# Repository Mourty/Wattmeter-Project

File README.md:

# The Wattmeter Project

This project was created for a senior design course as part of my degree path. I wanted to create a wattmeter similar to the "Kill A Watt" meters typically available, but with an important change. I wanted the ability to log the energy consumption data over time. I created a functional prototype well before I even began the class, but decided to iterate on the project and improve it. This is my first project of this scale, and I am sure it isn't perfect. In fact I'm sure it can be improved upon, but it works well enough for me.  
  
### Features
* Single Phase voltage, current, active power, reactive power, apparent power, frequency, and power factor measurement.
* LCD Display for user readable measurements.
* WiFi connectivity with RESTful API
* Configurable via SD card or web interface
* Dedicated Real time clock with automatic NTP syncing (WiFi required)
* Logs data to an SD card for optional independent operation
* Integrated UPS to prevent data loss due to power outage (100ish seconds plenty to automatically save data buffer)
* Monitoring server for remote data collection, storage, and presentation using React and python.

### Hardware
The hardware is a custom designed PCB with mostly through hole components. I chose through hole because it is what I wanted to use, more on this later.
The meter uses the Atmel M90E32 Poly-phase energy monitoring IC to do the heavy lifting of accurate power measurement. The voltage input uses a stepdown transformer and voltage divider to bring the 120VAC input voltage down around a manageable 0.6vrms. The transformer is somewhat unnecessary as a series of resistors could do the same, but this also provides some transient protection and isolation. The current measurement utilizes a current transformer with a carefully sizes burden resistor to bring the voltage down to around 0.6vrms when 20 amps is flowing though the primary of the CT. 
The power supply for the whole board is an off the shelf AC to DC power supply. This provides stable "safe" power without needed to roll my own PSU. This is fed to a super capacitor, then to the LM2621 based boost converted. The super capacitor provided an energy buffer to allow for controlled shutdown of the microcontroller in the event of a power outage. This allows time to write the current buffer of power statistics to the SD card. without this feature the SD card would either need to be written to more often with small amounts of data or the buffer would be lost during a power outage. Depending on the setting this could be multiple minutes or hours of data lost. The size of the super cap was chosen due to part availability at the time; It could easily be a quarter or even an eighth as large and still serve its purpose.
None of the components have been price optimized to a good degree. For example the diodes that are apart of the super capacitor/boost converter are rated for 2 amps, but don't ever see near that amount. These are simply what I had on hand during the design and didn't see a need to order different ones. So If you make this project too, you might want to consider components carefully, you might save some money.

I figured I could improve upon the wattmeter with the wattmeterJR. This version has fewer features, but is smaller and uses SMD components. It lacks an LCD display or the whole integrated UPS part. It is mainly to measure the same power statistics, but really requires the remote server to log the data. it is much less user friendly to build and to debug, but is cheaper and smaller. You can find this version at https://github.com/Mourty/WattmeterJR

### Firmware
I wrote the firmware with assistance from Claude.ai. I'm not the sort to go around proclaiming to be a coder, so you will find issues here. I used the Arduino IDE to develop, compile, and upload the code to the ESP32. The code is semi-organized into different files and imported where needed. The meter itself can be configured using the SD card. You will need to write the settings.ini to the SD card. In the settings you will find a place to configure your WiFi credentials as well as other settings. Many of these will seem cryptic, but most of them won't need to be modified at all. Most are actually configuration registers for the ATM90E32. You can find more on what the do in the IC's datasheet.  
  
### Service
The service is a web server that uses React for the front end and python for the backend. I again used Claude.ai to write much of the code here. The service is containerized using docker, so you should be able to get it up and running fairly easily. I used a Raspberry PI 3+, but in theory any linux computer can run this server. You will need to install docker to compose the containers and to run them. Docker *should* take care of installing other things for the containers like python and such.

I don't plan to maintain this or improve further at this time. If someone wants to improve this feel free, it won't hurt my feelings if you fork this project and do cool things with it, just give me credit for what you use. I have no idea what license this project should have given it uses a few external libraries, so before you go attempting to monetize this project you might need to check on that.

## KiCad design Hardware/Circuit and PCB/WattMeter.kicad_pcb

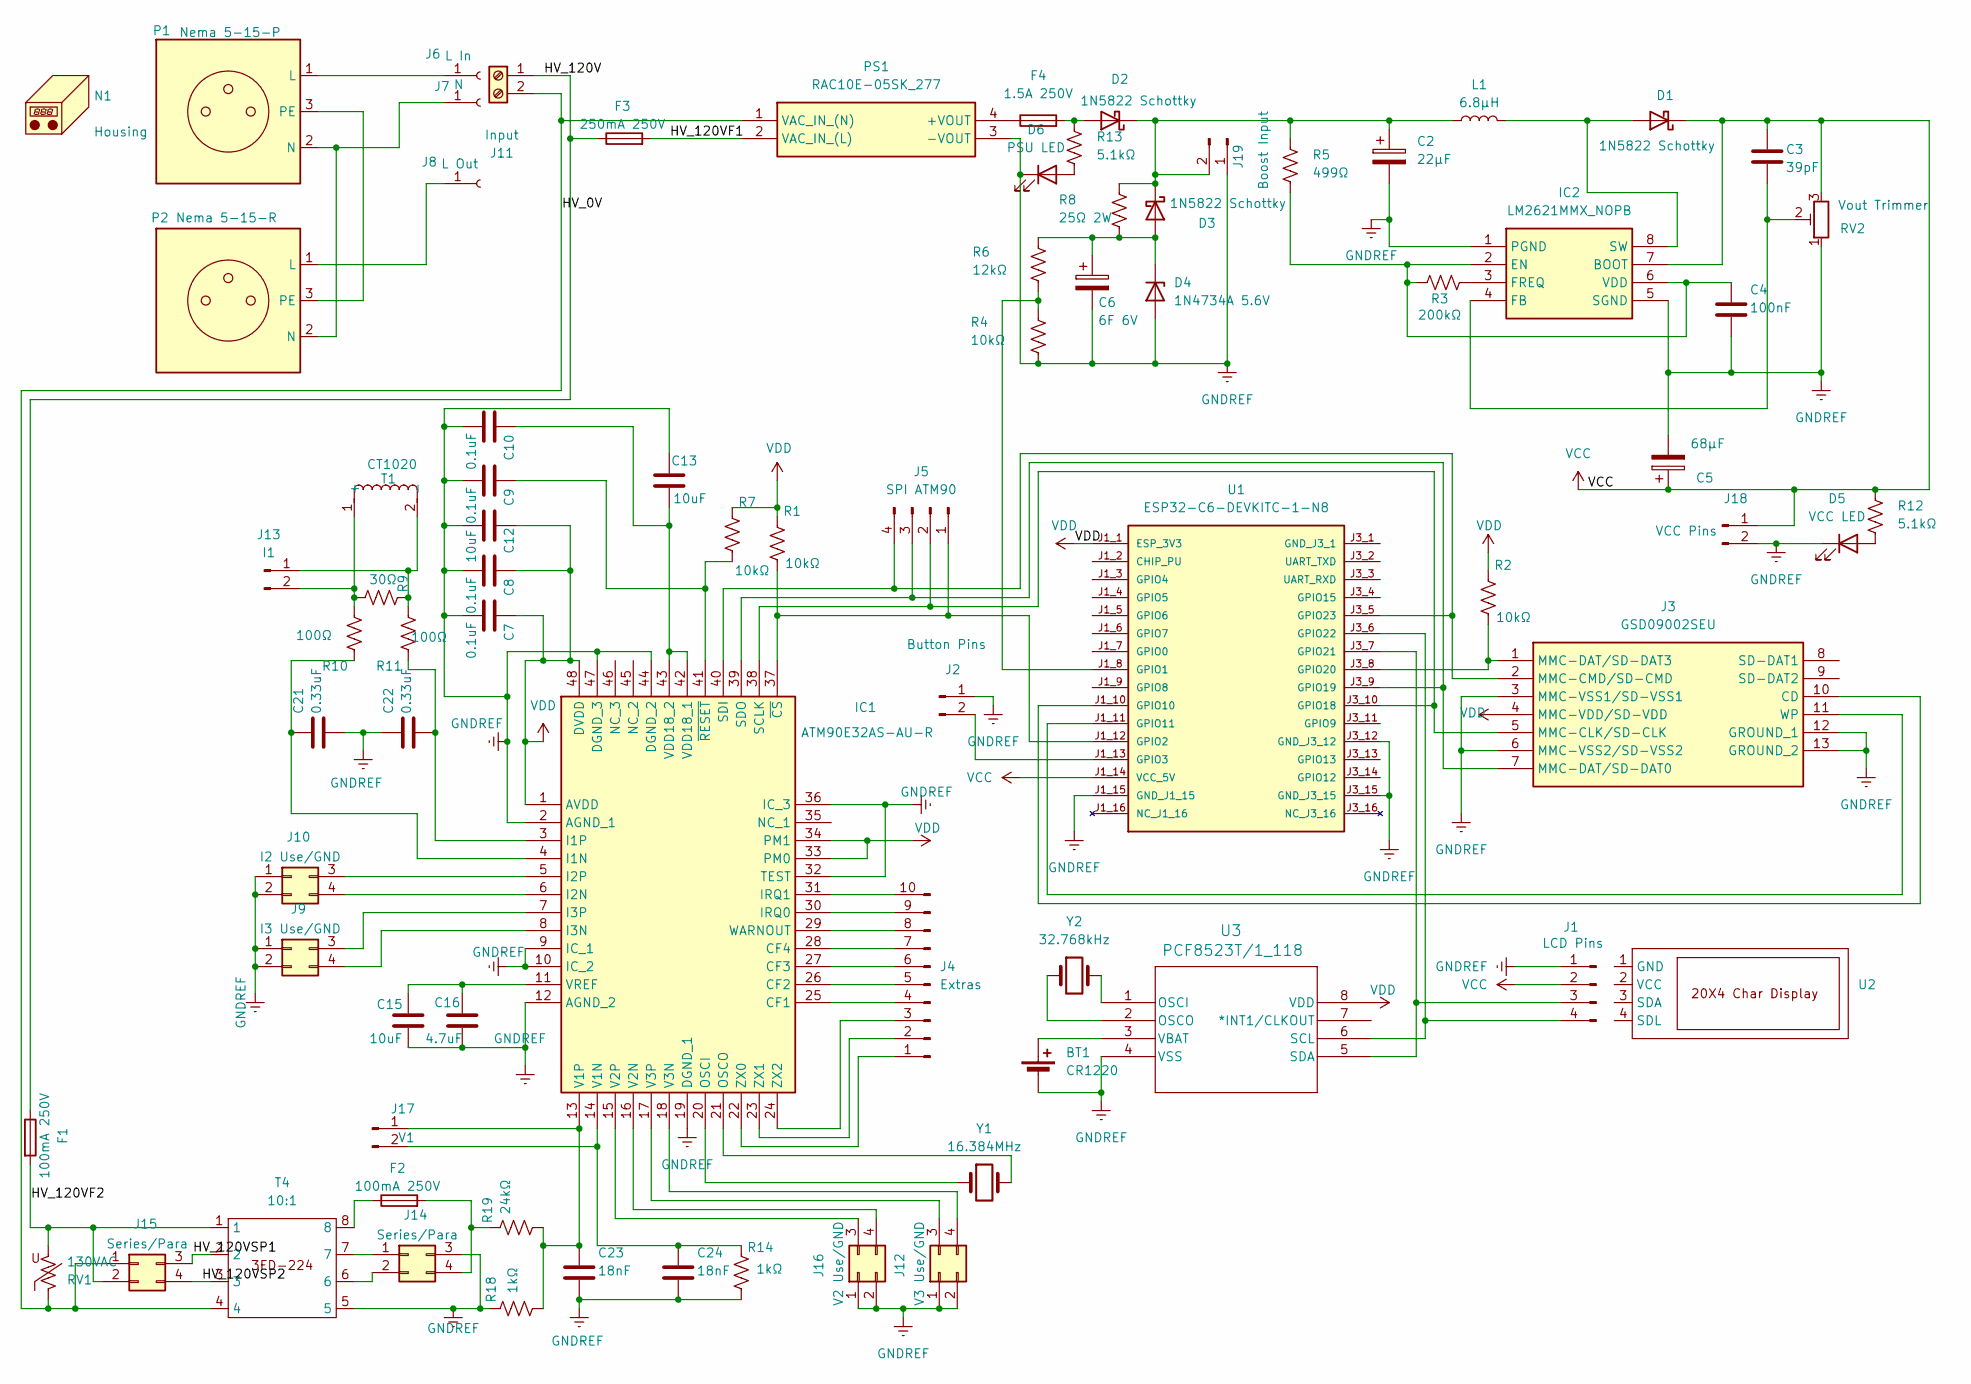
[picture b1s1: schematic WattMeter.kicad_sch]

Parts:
BT1: CR1220; BH127A1; Mouser# 737-BH-127A-1
C2: 22μF; CP_Radial_Tantal_D5.5mm_P5.00mm; Mouser# 581-TAP226K035CCS
C3: 39pF; C_Disc_D8.0mm_W5.0mm_P5.00mm; Mouser# 80-C317C390J2G
C4: 100nF; C_Disc_D8.0mm_W5.0mm_P5.00mm; Mouser# 594-K104K15X7RF53L2
C5: 68μF; CP_Radial_Tantal_D5.5mm_P5.00mm; Mouser# 581-TAP686K025CCS
C6: 6F 6V; C_Rect_L19.0mm_W11.0mm_P15.00mm_MKS4; Mouser# 815-ADCMS06R0SA605RB
C7, C8, C9, C10: 0.1uF; C_Disc_D6.0mm_W4.4mm_P5.00mm; Mouser# 594-K104K15X7RF5WH5
C12, C13, C15: 10uF; C_Disc_D5.0mm_W2.5mm_P2.50mm; Mouser# 810-FG18X5R1E106MR00
C16: 4.7uF; C_Disc_D5.0mm_W2.5mm_P2.50mm; Mouser# 810-FG28X5R1E475KRT6
C21, C22: 0.33uF; C_Disc_D5.0mm_W2.5mm_P2.50mm; Mouser# 810-FG18X7R1H334KRT6
C23, C24: 18nF; C_Disc_D5.0mm_W2.5mm_P5.00mm; Mouser# 594-K183K10X7RF53H5
D1, D2, D3: 1N5822 Schottky; D_DO-201AD_P15.24mm_Horizontal; Mouser# 511-1N5822
D4: 1N4734A 5.6V; D_DO-41_SOD81_P10.16mm_Horizontal; Mouser# 78-1N4734A
D5: VCC LED; LED_D5.0mm; Mouser# 859-LTL-4213
D6: PSU LED; LED_D5.0mm; Mouser# 859-LTL-4213
F1: 100mA 250V; 00318231; Mouser# 576-0313.100MXP
F2: 100mA 250V; Fuseholder_TR5_Littelfuse_No560_No460; Mouser# 693-0034.7105
F3: 250mA 250V; 00318231; Mouser# 576-0313.250HXP
F4: 1.5A 250V; Fuseholder_Clip-5x20mm_Keystone_3512P_Inline_P23.62x7.27mm_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
IC1: ATM90E32AS-AU-R; QFP50P900X900X120-48N; Mouser# 556-ATM90E32AS-AU-R
IC2: LM2621MMX_NOPB; SOP65P490X110-8N; Mouser# 926-LM2621MMX/NOPB
J1: LCD Pins; PinHeader_1x04_P2.54mm_Vertical; Mouser# 910-HDR100IMP40MGVTH
J2: Button Pins; PinHeader_1x02_P2.54mm_Vertical; Mouser# 910-HDR100IMP40MGVTH
J3: GSD09002SEU; Mouser# 523-GSD09002SEU
J4: Extras; PinHeader_1x10_P2.54mm_Vertical; Mouser# 910-HDR100IMP40MGVTH
J5: SPI ATM90; PinHeader_1x04_P2.54mm_Vertical; Mouser# 910-HDR100IMP40MGVTH
J6: L In
J7: N
J8: L Out
J9: I3 Use/GND; PinHeader_2x02_P2.54mm_Vertical; Mouser# 910-HDR100IMP40MGVTH
J10: I2 Use/GND; PinHeader_2x02_P2.54mm_Vertical; Mouser# 910-HDR100IMP40MGVTH
J11: Input; CUI_TB005-762-02BE; Mouser# 490-TB005-762-02BE
J12: V3 Use/GND; PinHeader_2x02_P2.54mm_Vertical; Mouser# 910-HDR100IMP40MGVTH
J13: I1; PinHeader_1x02_P2.54mm_Vertical; Mouser# 910-HDR100IMP40MGVTH
J14, J15: Series/Para; PinHeader_2x02_P2.54mm_Vertical; Mouser# 910-HDR100IMP40MGVTH
J16: V2 Use/GND; PinHeader_2x02_P2.54mm_Vertical; Mouser# 910-HDR100IMP40MGVTH
J17: V1; PinHeader_1x02_P2.54mm_Vertical; Mouser# 910-HDR100IMP40MGVTH
J18: VCC Pins; PinHeader_1x02_P2.54mm_Vertical; Mouser# 910-HDR100IMP40MGVTH
J19: Boost Input; PinHeader_1x02_P2.54mm_Vertical; Mouser# 910-HDR100IMP40MGVTH
L1: 6.8μH; L_Radial_D12.0mm_P5.00mm_Fastron_11P; Mouser# 994-RFS1113-682ME
N1: Housing; 1591XXF Enclosure 4 point; Mouser# 546-1591XXFBK
P1: Nema 5-15-P
P2: Nema 5-15-R
PS1: RAC10E-05SK_277; RAC10E05SK277; Mouser# 919-RAC10E-05SK/277
R1, R2, R4, R7: 10kΩ; R_Axial_DIN0207_L6.3mm_D2.5mm_P10.16mm_Horizontal; Mouser# 603-MFR-25FTE52-10K
R3: 200kΩ; R_Axial_DIN0207_L6.3mm_D2.5mm_P10.16mm_Horizontal; Mouser# 603-MFR-25FBF52-200K
R5: 499Ω; R_Axial_DIN0207_L6.3mm_D2.5mm_P10.16mm_Horizontal; Mouser# 603-MFR-25FBF52-499R
R6: 12kΩ; R_Axial_DIN0207_L6.3mm_D2.5mm_P10.16mm_Horizontal; Mouser# 603-MFR-25FBF52-12K
R8: 25Ω 2W; R_Axial_DIN0414_L11.9mm_D4.5mm_P5.08mm_Vertical; Mouser# 588-WNC25RFET
R9: 30Ω; R_Axial_DIN0207_L6.3mm_D2.5mm_P10.16mm_Horizontal; Mouser# 603-MFR-25FBF52-30R
R10, R11: 100Ω; R_Axial_DIN0207_L6.3mm_D2.5mm_P10.16mm_Horizontal; Mouser# MFR-25FBF52-100R
R12, R13: 5.1kΩ; R_Axial_DIN0207_L6.3mm_D2.5mm_P10.16mm_Horizontal; Mouser# 603-MFR-25FBF52-5K1
R14, R18: 1kΩ; R_Axial_DIN0207_L6.3mm_D2.5mm_P10.16mm_Horizontal; Mouser# 603-MFR-25FBF52-1K
R19: 24kΩ; R_Axial_DIN0207_L6.3mm_D2.5mm_P10.16mm_Horizontal; Mouser# 603-MFR-25FBF52-24K
RV1: 130VAC; C_Disc_D8.0mm_W5.0mm_P5.00mm; Mouser# 576-V07E130P
RV2: Vout Trimmer; Potentiometer_Bourns_3266Y_Vertical; Mouser# 81-PV36W204C01B00
T1: CT1020; Manufacturer_Part_Number CS1100L; Digikey# 419-CT1020-ND
T4: 10:1; 3FD-224; Mouser# 838-3FD-224
U1: ESP32-C6-DEVKITC-1-N8; MODULE_ESP32-C6-DEVKITC-1-N8; PARTREV 1.3; Mouser# 356-ESP32C6DKC1N8
U2: (no value)
U3: PCF8523T/1_118; SO8_SOT96-1_NXP; Digikey# 568-5306-1-ND
Y1: 16.384MHz; Crystal_HC49-U_Vertical; Mouser# 815-ABL-16.384-B2
Y2: 32.768kHz; Crystal_DS26_D2.0mm_L6.0mm_Horizontal; Mouser# 815-ABL-16.384-B2

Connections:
/HV_0V: J11.2, J15.1, PS1.1 (VAC_IN_(N)), RV1.1, T4.4
/HV_120V: F1.1, F3.1, J11.1
/HV_120VF1: F3.2, PS1.2 (VAC_IN_(L))
/HV_120VF2: F1.2, J15.2, RV1.2, T4.1
/HV_120VSP1: J15.3, T4.2
/HV_120VSP2: J15.4, T4.3
GNDREF: BT1.2 (-), C2.2, C4.2, C5.2, C6.2, C7.2, C8.2, C9.2, C10.2, C12.1, C13.2, C15.2, C16.2, C21.2, C22.1, C23.2, C24.2, D4.2 (A), D5.1 (K), D6.1 (K), IC1.2 (AGND_1), IC1.9 (IC_1), IC1.10 (IC_2), IC1.12 (AGND_2), IC1.19 (DGND_1), IC1.32 (TEST), IC1.36 (IC_3), IC1.44 (DGND_2), IC1.47 (DGND_3), IC2.1 (PGND), IC2.5 (SGND), J1.1, J2.1, J3.3 (MMC-VSS1/SD-VSS1), J3.6 (MMC-VSS2/SD-VSS2), J3.12 (GROUND_1), J3.13 (GROUND_2), J9.1, J9.2, J10.1, J10.2, J12.1, J12.2, J14.3, J16.1, J16.2, J18.2, J19.1, PS1.3 (-VOUT), R4.1, R14.1, R18.2, RV2.1, T4.5, U1.J1_15 (GND_J1_15), U1.J3_12 (GND_J3_12), U1.J3_15 (GND_J3_15), U3.4 (VSS)
unnamed: BT1.1 (+), U3.3 (VBAT)
unnamed: D1.2 (A), IC2.8 (SW), L1.2
unnamed: D2.2 (A), F4.2, R13.2
unnamed: C2.1, D2.1 (K), D3.1 (K), J19.2, L1.1, R5.2, R8.2
unnamed: C6.1, D3.2 (A), D4.1 (K), R6.2, R8.1
unnamed: D5.2 (A), R12.1
unnamed: D6.2 (A), R13.1
unnamed: F2.1, T4.8
unnamed: IC1.25 (CF1), J4.4
unnamed: IC1.26 (CF2), J4.5
unnamed: IC1.27 (CF3), J4.6
unnamed: IC1.28 (CF4), J4.7
unnamed: C21.1, IC1.4 (I1N), R10.2
unnamed: C22.2, IC1.3 (I1P), R11.2
unnamed: IC1.6 (I2N), J10.4
unnamed: IC1.5 (I2P), J10.3
unnamed: IC1.8 (I3N), J9.4
unnamed: IC1.7 (I3P), J9.3
unnamed: IC1.30 (IRQ0), J4.9
unnamed: IC1.31 (IRQ1), J4.10
unnamed: IC1.20 (OSCI), Y1.1
unnamed: IC1.21 (OSCO), Y1.2
unnamed: IC1.38 (SCLK), J3.5 (MMC-CLK/SD-CLK), J5.2, U1.J3_10 (GPIO18)
unnamed: IC1.40 (SDI), J3.2 (MMC-CMD/SD-CMD), J5.4, U1.J3_5 (GPIO23)
unnamed: IC1.39 (SDO), J3.7 (MMC-DAT/SD-DAT0), J5.3, U1.J3_9 (GPIO19)
unnamed: C24.1, IC1.14 (V1N), J17.2, R14.2
unnamed: C23.1, IC1.13 (V1P), J17.1, R18.1, R19.1
unnamed: IC1.16 (V2N), J16.4
unnamed: IC1.15 (V2P), J16.3
unnamed: IC1.18 (V3N), J12.4
unnamed: IC1.17 (V3P), J12.3
unnamed: C10.1, C13.1, IC1.42 (VDD18_1), IC1.43 (VDD18_2)
unnamed: C15.1, C16.1, IC1.11 (VREF)
unnamed: IC1.29 (WARNOUT), J4.8
unnamed: IC1.22 (ZX0), J4.1
unnamed: IC1.23 (ZX1), J4.2
unnamed: IC1.24 (ZX2), J4.3
unnamed: IC1.37 (~CS), J5.1, R1.1, U1.J1_12 (GPIO2)
unnamed: C9.1, IC1.41 (~RESET), R7.1
unnamed: C4.1, IC2.2 (EN), IC2.6 (VDD), R3.1, R5.1
unnamed: C3.2, IC2.4 (FB), RV2.2
unnamed: IC2.3 (FREQ), R3.2
unnamed: J1.3, U1.J3_7 (GPIO21), U3.5 (SDA)
unnamed: J1.4, U1.J3_6 (GPIO22), U3.6 (SCL)
unnamed: J2.2, U1.J1_13 (GPIO3)
unnamed: J3.10 (CD), U1.J1_10 (GPIO10)
unnamed: J3.1 (MMC-DAT/SD-DAT3), R2.1, U1.J3_8 (GPIO20)
unnamed: J3.11 (WP), U1.J1_11 (GPIO11)
unnamed: J6.1, P1.1 (L)
unnamed: J7.1, P1.2 (N), P2.2 (N)
unnamed: J8.1, P2.1 (L)
unnamed: J13.1, R9.2, R11.1, T1.2 (-)
unnamed: J13.2, R9.1, R10.1, T1.1 (+)
unnamed: J14.1, T4.7
unnamed: J14.2, T4.6
unnamed: F2.2, J14.4, R19.2
unnamed: P1.3 (PE), P2.3 (PE)
unnamed: F4.1, PS1.4 (+VOUT)
unnamed: R4.2, R6.1, U1.J1_8 (GPIO1)
unnamed: U3.1 (OSCI), Y2.2
unnamed: U3.2 (OSCO), Y2.1
VCC: C3.1, C5.1, D1.1 (K), IC2.7 (BOOT), J1.2, J18.1, R12.2, RV2.3, U1.J1_14 (VCC_5V)
VDD: C7.1, C8.1, C12.2, IC1.1 (AVDD), IC1.33 (PM0), IC1.34 (PM1), IC1.48 (DVDD), J3.4 (MMC-VDD/SD-VDD), R1.2, R2.2, R7.2, U1.J1_1 (ESP_3V3), U3.8 (VDD)

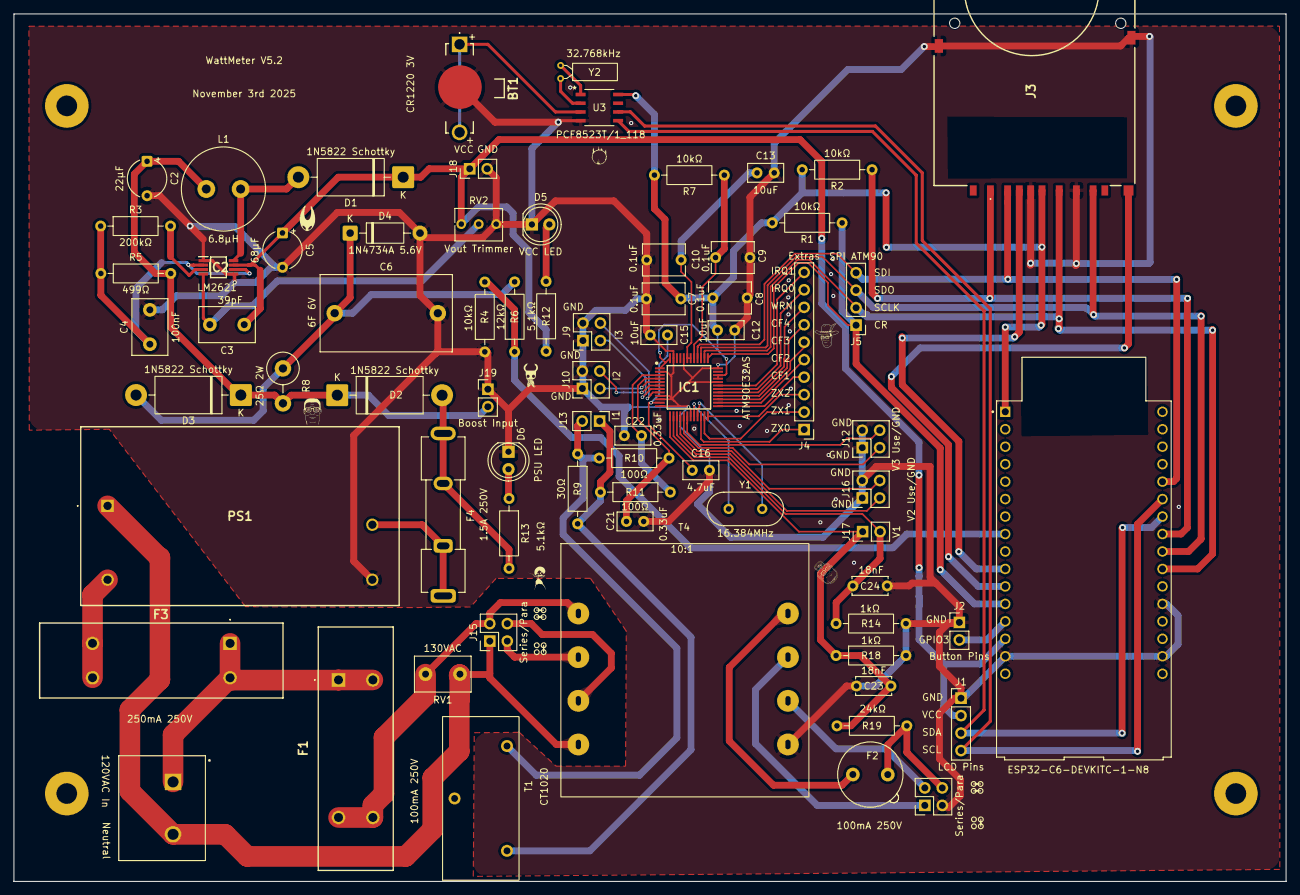
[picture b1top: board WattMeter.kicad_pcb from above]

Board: 2 copper layers, 185.0 x 126.1 mm, 73 parts (0 on the bottom side), 66 nets.

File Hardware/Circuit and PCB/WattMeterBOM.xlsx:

Reference | Qty | Value | Mouser# | Digikey# | Amazon Link | Price/unit | Line Price
BT1 | 1 | CR1220 | 737-BH-127A-1 |  |  | 0.3 | 0.3
C12,C13,C15 | 3 | 10uF | 810-FG18X5R1E106MR00 |  |  | 0.27800000000000002 | 0.83399999999999996
C16 | 1 | 4.7uF | 810-FG28X5R1E475KRT6 |  |  | 0.22 | 0.22
C2 | 1 | 22μF | 581-TAP226K035CCS |  |  | 1.05 | 1.05
C21,C22 | 2 | 0.33uF | 810-FG18X7R1H334KRT6 |  |  | 0.115 | 0.23
C23,C24 | 2 | 18nF | 594-K183K10X7RF53H5 |  |  | 0.121 | 0.24199999999999999
C3 | 1 | 39pF | 80-C317C390J2G |  |  | 0.12 | 0.12
C4 | 1 | 100nF | 594-K104K15X7RF53L2 |  |  | 0.106 | 0.106
C5 | 1 | 68μF | 581-TAP686K025CCS |  |  | 2.1800000000000002 | 2.1800000000000002
C6 | 1 | 6F 6V | 815-ADCMS06R0SA605RB |  |  | 5.51 | 5.51
C7,C8,C9,C10 | 4 | 0.1uF | 594-K104K15X7RF5WH5 |  |  | 8.8999999999999996E-2 | 0.35599999999999998
D1,D2,D3 | 3 | 1N5822 Schottky | 511-1N5822 |  |  | 0.28000000000000003 | 0.84
D4 | 1 | 1N4734A 5.6V | 78-1N4734A |  |  | 5.1999999999999998E-2 | 5.1999999999999998E-2
D5 | 1 | VCC LED | 859-LTL-4213 |  |  | 8.7999999999999995E-2 | 8.7999999999999995E-2
D6 | 1 | PSU LED | 859-LTL-4213 |  |  | 8.7999999999999995E-2 | 8.7999999999999995E-2
F1 | 1 | 100mA 250V | 576-0313.100MXP |  |  | 2.29 | 2.29
F2 | 1 | 100mA 250V | 693-0034.7105 |  |  | 0.81399999999999995 | 0.81399999999999995
F3 | 1 | 250mA 250V | 576-0313.250HXP |  |  | 1.43 | 1.43
F4 | 1 | 1.5A 250V |  |  | https://www.amazon.com/dp/B07MCHQQ7Z?ref=ppx_yo2ov_dt_b_fed_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 | 1.67 | 1.67
IC1 | 1 | ATM90E32AS-AU-R | 556-ATM90E32AS-AU-R |  |  | 3.66 | 3.66
IC2 | 1 | LM2621MMX_NOPB | 926-LM2621MMX/NOPB |  |  | 1.77 | 1.77
J1 | 1 | LCD Pins | 910-HDR100IMP40MGVTH |  |  | 5.8000000000000003E-2 | 5.8000000000000003E-2
J10 | 1 | I2 Use/GND | 910-HDR100IMP40MGVTH |  |  | 5.8000000000000003E-2 | 5.8000000000000003E-2
J11 | 1 | Input | 490-TB005-762-02BE |  |  | 0.66 | 0.66
J12 | 1 | V3 Use/GND | 910-HDR100IMP40MGVTH |  |  | 5.8000000000000003E-2 | 5.8000000000000003E-2
J13 | 1 | I1 | 910-HDR100IMP40MGVTH |  |  | 2.9000000000000001E-2 | 2.9000000000000001E-2
J14,J15 | 2 | Series/Para | 910-HDR100IMP40MGVTH |  |  | 5.8000000000000003E-2 | 0.11600000000000001
J16 | 1 | V2 Use/GND | 910-HDR100IMP40MGVTH |  |  | 5.8000000000000003E-2 | 5.8000000000000003E-2
J17 | 1 | V1 | 910-HDR100IMP40MGVTH |  |  | 2.9000000000000001E-2 | 2.9000000000000001E-2
J18 | 1 | VCC Pins | 910-HDR100IMP40MGVTH |  |  | 2.9000000000000001E-2 | 2.9000000000000001E-2
J19 | 1 | Boost Input | 910-HDR100IMP40MGVTH |  |  | 2.9000000000000001E-2 | 2.9000000000000001E-2
J2 | 1 | Button Pins | 910-HDR100IMP40MGVTH |  |  | 1.4500000000000001E-2 | 1.4500000000000001E-2
J3 | 1 | GSD09002SEU | 523-GSD09002SEU |  |  | 1.4 | 1.4
J4 | 1 | Extras | 910-HDR100IMP40MGVTH |  |  | 0.14499999999999999 | 0.14499999999999999
J5 | 1 | SPI ATM90 | 910-HDR100IMP40MGVTH |  |  | 5.8000000000000003E-2 | 5.8000000000000003E-2
J9 | 1 | I3 Use/GND | 910-HDR100IMP40MGVTH |  |  | 5.8000000000000003E-2 | 5.8000000000000003E-2
L1 | 1 | 6.8μH | 994-RFS1113-682ME |  |  | 1.65 | 1.65
N1 | 1 | Housing | 546-1591XXFBK |  |  | 19.07 | 19.07
P1 | 1 | Nema 5-15-P |  |  | https://www.amazon.com/Leviton-515PR-Straight-Blade-Rubber/d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 | 3.98 | 3.98
P2 | 1 | Nema 5-15-R |  |  | https://www.amazon.com/dp/B0BMV8DSM1?ref=ppx_yo2ov_dt_b_fed_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 | 9.99 | 9.99
PS1 | 1 | RAC10E-05SK_277 | 919-RAC10E-05SK/277 |  |  | 9.64 | 9.64
R1,R2,R4,R7 | 4 | 10kΩ | 603-MFR-25FTE52-10K |  |  | 2.8000000000000001E-2 | 0.112
R10,R11 | 2 | 100Ω | MFR-25FBF52-100R |  |  | 2.9000000000000001E-2 | 5.8000000000000003E-2
R12,R13 | 2 | 5.1kΩ | 603-MFR-25FBF52-5K1 |  |  | 2.9000000000000001E-2 | 5.8000000000000003E-2
R14,R18 | 2 | 1kΩ | 603-MFR-25FBF52-1K |  |  | 2.5999999999999999E-2 | 5.1999999999999998E-2
R19 | 1 | 24kΩ | 603-MFR-25FBF52-24K |  |  | 2.9000000000000001E-2 | 2.9000000000000001E-2
R3 | 1 | 200kΩ | 603-MFR-25FBF52-200K |  |  | 2.9000000000000001E-2 | 2.9000000000000001E-2
R5 | 1 | 499Ω | 603-MFR-25FBF52-499R |  |  | 2.7E-2 | 2.7E-2
R6 | 1 | 12kΩ | 603-MFR-25FBF52-12K |  |  | 2.9000000000000001E-2 | 2.9000000000000001E-2
R8 | 1 | 25Ω 2W | 588-WNC25RFET |  |  | 1.46 | 1.46
R9 | 1 | 30Ω | 603-MFR-25FBF52-30R |  |  | 2.9000000000000001E-2 | 2.9000000000000001E-2
RV1 | 1 | 130VAC | 576-V07E130P |  |  | 0.186 | 0.186
RV2 | 1 | Vout Trimmer | 81-PV36W204C01B00 |  |  | 1.21 | 1.21
T1 | 1 | CT1020 |  | 419-CT1020-ND |  | 6.04 | 6.04
T4 | 1 | 10 to 1 | 838-3FD-224 |  |  | 4.5 | 4.5
U1 | 1 | ESP32-C6-DEVKITC-1-N8 | 356-ESP32C6DKC1N8 |  |  | 8.76 | 8.76
U2 | 1 | ~ |  |  | https://www.amazon.com/dp/B0C1G9GBRZ?ref=ppx_yo2ov_dt_b_fed_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 | 5.66 | 5.66
U3 | 1 | PCF8523T/1_118 |  | 568-5306-1-ND |  | 1.29 | 1.29
Y1 | 1 | 16.384MHz | 815-ABL-16.384-B2 |  |  | 0.32 | 0.32
Y2 | 1 | 32.768kHz | 815-ABL-16.384-B2 |  |  | 0.32 | 0.32
Total |  |  |  |  |  |  | 101.14849999999998

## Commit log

2025-12-10 Add some plots
2026-01-04 Add Pictures
2026-01-04 Add Board Render
